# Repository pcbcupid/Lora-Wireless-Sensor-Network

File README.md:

# Lora-Wireless-Sensor-Network

This repo will teach you, how to build a hardware product based on WSN completely from scratch!

We'll walk you through all the stages : 
* [Purpose](https://www.youtube.com/watch?v=e1ifblb0CRQ)
* [Brainstroming -> Feature Selection](https://www.youtube.com/watch?v=0gfi7CeLzbg)
* [Features -> Component Selection](https://youtu.be/0gfi7CeLzbg?t=293)
* [Component -> Schematic Design](https://www.youtube.com/watch?v=nbiwXsXPYxc)
* [Schematic Design -> PCB Design](https://www.youtube.com/watch?v=FiMsBjr6rtk)
* [PCB -> Mechanical Case Design](https://youtu.be/7FC-pByCCXM?si=cBypyLcrKBF-iJE6)
* [Finished Hardware + Code](https://github.com/pcbcupid/Lora-Wireless-Sensor-Network/tree/main/Code)
* [Final Testing](https://www.youtube.com/watch?v=_qDI99OTmmE)

### PCB DESIGN

###### MASTER NODE 

###### SLAVE NODE

### PCB ASSEMBLED 

###### MASTER NODE

###### SLAVE NODE 

### CAD DESIGN 

###### MASTER NODE 

###### SLAVE NODE

### 3D PRINTING 

###### MASTER NODE CASE 

###### SLAVE NODE CASE

### FINAL SETUP 

###### MASTER NODE SETUP 

###### SLAVE NODE SETUP

### DASHBOARD UI

###### MASTER CLOUD DASHBOARD

###### SLAVE CLOUD DASHBOARD

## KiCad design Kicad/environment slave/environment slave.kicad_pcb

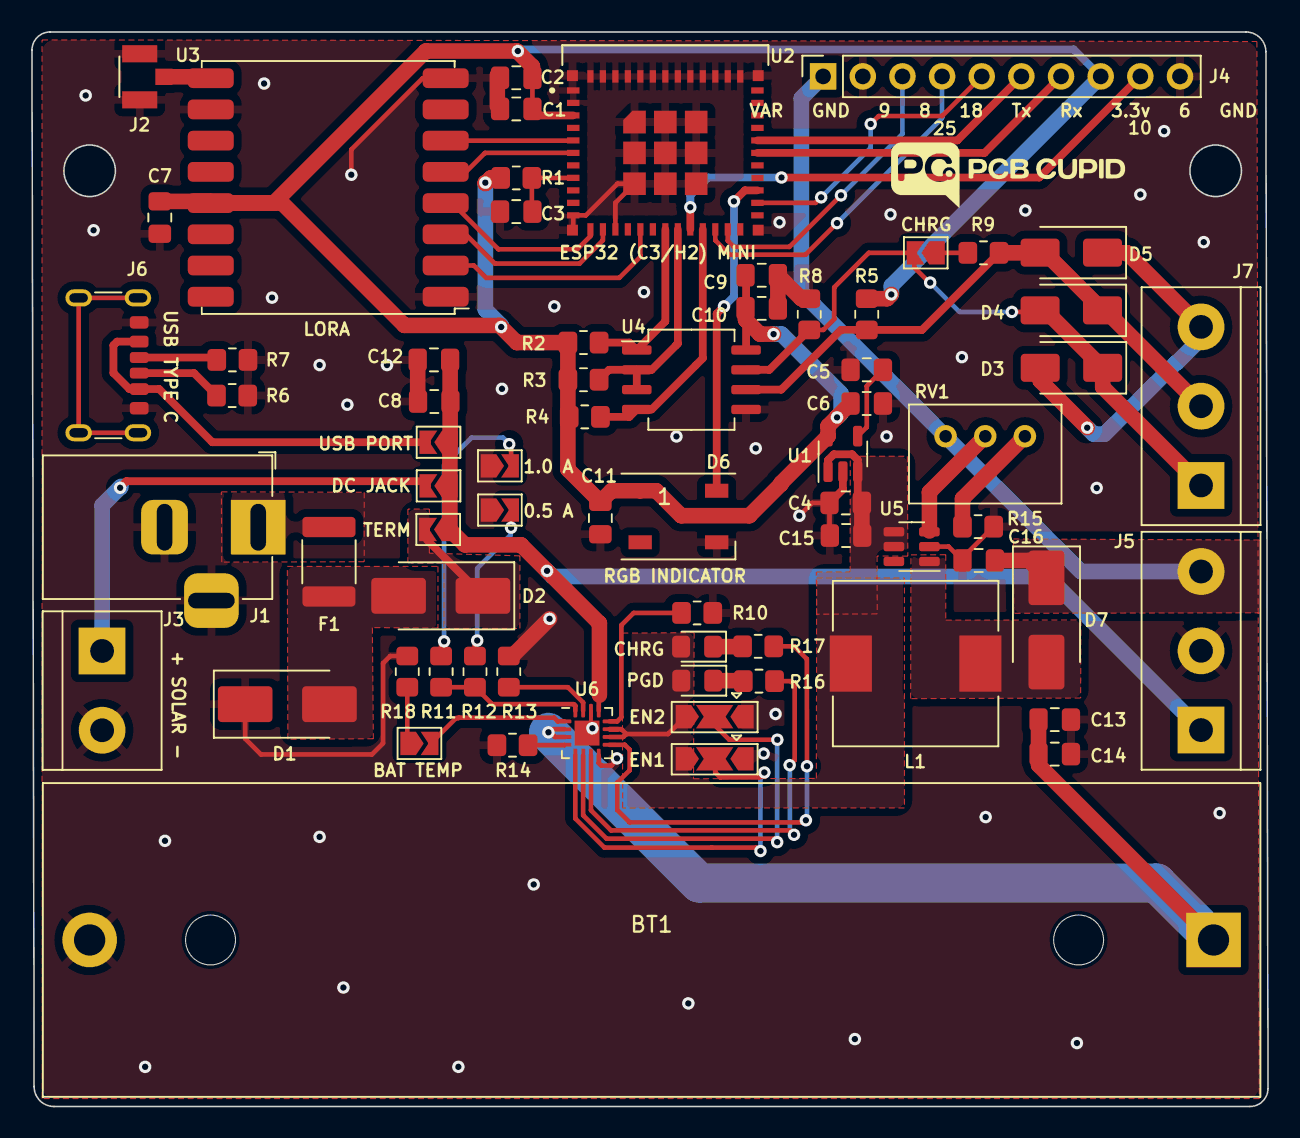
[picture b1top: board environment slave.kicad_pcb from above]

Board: 2 copper layers, 79.2 x 68.8 mm, 69 parts (0 on the bottom side), 52 nets.

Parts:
BT1: Battery_Cell; BatteryHolder_MPD_BH-18650-PC2
C1, C8, C10, C12, C13, C14: 10uf; C_0805_2012Metric_Pad1.18x1.45mm_HandSolder
C2, C4, C7, C11: 0.1uf; C_0805_2012Metric_Pad1.18x1.45mm_HandSolder
C3: 1uf; C_0805_2012Metric_Pad1.18x1.45mm_HandSolder
C5: 470pf; C_0805_2012Metric_Pad1.18x1.45mm_HandSolder
C6: 2.2uf; C_0805_2012Metric_Pad1.18x1.45mm_HandSolder
C9: 0.1uF; C_0805_2012Metric_Pad1.18x1.45mm_HandSolder
C15, C16: 22uf; C_0805_2012Metric_Pad1.18x1.45mm_HandSolder
D1: SMAJ24; D_SMB_Handsoldering
D2: SS34; D_SMB_Handsoldering
D3, D4, D5: SMAJ6.8CA; D_SMA
D6: WS2812B; LED_WS2812B_PLCC4_5.0x5.0mm_P3.2mm
D7: D; D_SMB_Handsoldering
D8: LED - Green; LED_0805_2012Metric_Pad1.15x1.40mm_HandSolder
D9: LED - RED; LED_0805_2012Metric_Pad1.15x1.40mm_HandSolder
F1: Polyfuse; Fuse_1812_4532Metric_Pad1.30x3.40mm_HandSolder
J1: Barrel_Jack; BarrelJack_Horizontal
J2: U.FL-R-SMT_01_; HRS_U.FL-R-SMT_01_
J3: Solar; TerminalBlock_bornier-2_P5.08mm
J4: Conn_01x10; PinSocket_1x10_P2.54mm_Vertical
J5: PWR OUT; TerminalBlock_bornier-3_P5.08mm
J6: USB_C_Receptacle_PowerOnly_6P; USB_C_Receptacle_GCT_USB4125-xx-x_6P_TopMnt_Horizontal
J7: RS485 OUT; TerminalBlock_bornier-3_P5.08mm
JP1, JP2, JP4, JP9: T-JMP; SolderJumper-2_P1.3mm_Open_TrianglePad1.0x1.5mm
JP3: NO; SolderJumper-2_P1.3mm_Open_TrianglePad1.0x1.5mm
JP5: E1; SolderJumper-3_P2.0mm_Open_TrianglePad1.0x1.5mm
JP6: E2; SolderJumper-3_P2.0mm_Open_TrianglePad1.0x1.5mm
JP7: 1A JMP; SolderJumper-2_P1.3mm_Open_TrianglePad1.0x1.5mm
JP8: 0.5A JMP; SolderJumper-2_P1.3mm_Open_TrianglePad1.0x1.5mm
L1: L; L_10.4x10.4_H4.8
R1, R2, R3, R4, R13, R14, R16, R17: 10k; R_0805_2012Metric_Pad1.20x1.40mm_HandSolder
R5, R8: 20k; R_0805_2012Metric_Pad1.20x1.40mm_HandSolder
R6, R7: 5.1k; R_0805_2012Metric_Pad1.20x1.40mm_HandSolder
R9: 120R; R_0805_2012Metric_Pad1.20x1.40mm_HandSolder
R10, R11, R18: 1k; R_0805_2012Metric_Pad1.20x1.40mm_HandSolder
R12: 2k; R_0805_2012Metric_Pad1.20x1.40mm_HandSolder
R15: 2.2k; R_0805_2012Metric_Pad1.20x1.40mm_HandSolder
RV1: 100k; Potentiometer_Bourns_3299W_Vertical
U1: MIC5219-3.3v; SOT-23-5
U2: ESP32-C3-MINI-1U-N4; XCVR_ESP32-C3-MINI-1U-N4
U3: RFM95W-868S2; HOPERF_RFM9XW_SMD
U4: THVD1406; SO-8_5.3x6.2mm_P1.27mm
U5: MT3608; SOT-23-6
U6: BQ24074RGT; VQFN-16-1EP_3x3mm_P0.5mm_EP1.6x1.6mm

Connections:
+3.3V: C1.1, C2.1, C6.1, C7.1, C9.1, C10.1, C11.1, D6.1 (VDD), J4.8, R1.1, R2.1, R3.1, R4.1, R5.1, U1.5 (OUT), U2.3 (3V3), U3.13 (3.3V), U4.8 (VCC)
/Battery Managment Circuit/Bat+: BT1.1 (+), C13.1, C14.1, U6.2 (BAT), U6.3 (BAT)
/COM: D3.2 (A2), D5.1 (A1), J7.3
/DI: R4.2, U2.21 (IO7), U4.4 (DI)
/DTR: R3.2, U2.19 (IO5), U4.2 (~RE), U4.3 (DE)
/GPIO6: J4.9, U2.20 (IO6)
/GPIO8: J4.4, U2.22 (IO8)
/GPIO9: J4.3, U2.23 (IO9)
/GPIO18: J4.5, U2.26 (IO18)
/MISO: U2.16 (IO10), U3.2 (MISO)
/MOSI: U2.13 (IO1), U3.3 (MOSI)
/NSS: U2.6 (IO3), U3.5 (NSS)
/OUT: C4.1, C15.1, D8.2 (A), D9.2 (A), JP5.3 (B), JP6.3 (B), L1.1, U1.1 (IN), U1.3 (EN), U5.4 (EN), U5.5 (IN), U6.10 (OUT), U6.11 (OUT)
/OUT_VAR: C16.1, D7.1 (K), J4.1, J5.3, RV1.3
/R0: R2.2, U2.18 (IO4), U4.1 (RO)
/RESET: U2.5 (IO2), U3.6 (RESET)
/RGB: D6.4 (DIN), U2.27 (IO19)
/SCK: U2.12 (IO0), U3.4 (SCK)
/U0Rxd: J4.7, U2.30 (RXD0)
/U0Txd: J4.6, U2.31 (TXD0)
GND: BT1.2 (-), C1.2, C2.2, C3.2, C4.2, C5.2, C6.2, C7.2, C8.2, C9.2, C10.2, C11.2, C12.2, C13.2, C14.2, C15.2, C16.2, D1.1 (A1), D6.3 (VSS), J1.2, J1.3, J2.1 (GND), J2.2 (GND), J3.2, J4.2, J4.10, J5.2, J6.A12 (GND), J6.B12 (GND), JP5.1 (A), JP6.1 (A), JP7.1 (A), JP8.1 (A), R6.1, R7.1, R8.2, R10.1, R13.1, R14.1, R15.2, R18.2, U1.2 (GND), U2.1 (GND), U2.2 (GND__1), U2.11 (GND__2), U2.14 (GND__3), U2.36 (GND__4), U2.37 (GND__5), U2.38 (GND__6), U2.39 (GND__7), U2.40 (GND__8), U2.41 (GND__9), U2.42 (GND__10), U2.43 (GND__11), U2.44 (GND__12), U2.45 (GND__13), U2.46 (GND__14), U2.47 (GND__15), U2.48 (GND__16), U2.49_1 (GND__17), U2.49_2 (GND__18), U2.49_3 (GND__19), U2.49_4 (GND__20), U2.49_5 (GND__21), U2.49_6 (GND__22), U2.49_7 (GND__23), U2.49_8 (GND__24), U2.49_9 (GND__25), U2.50 (GND__26), U2.51 (GND__27), U2.52 (GND__28), U2.53 (GND__29), U3.1 (GND), U3.8 (GND), U3.10 (GND), U4.5 (GND), U5.2 (GND), U6.8 (VSS), U6.14 (TMR), U6.17 (VSS)
unnamed: D1.2 (A2), D2.2 (A), F1.2
unnamed: D2.1 (K), JP1.2 (B)
unnamed: D3.1 (A1), D4.2 (A2), J7.1, JP3.2 (B), R8.1, U4.7 (B)
unnamed: D4.1 (A1), D5.2 (A2), J7.2, R5.2, R9.2, U4.6 (A)
unnamed: D7.2 (A), L1.2, U5.1 (SW)
unnamed: D8.1 (K), R16.2
unnamed: D9.1 (K), R17.2
unnamed: F1.1, J1.1
unnamed: J2.3 (SIG), U3.9 (ANT)
unnamed: J3.1, JP2.2 (B)
unnamed: J6.A5 (CC1), R7.2
unnamed: J6.B5 (CC2), R6.2
unnamed: JP3.1 (A), R9.1
unnamed: J6.A9 (VBUS), J6.B9 (VBUS), JP4.2 (B)
unnamed: JP5.2 (C), U6.5 (EN2)
unnamed: JP6.2 (C), U6.6 (EN1)
unnamed: JP7.2 (B), R11.1
unnamed: JP8.2 (B), R12.1
unnamed: JP9.1 (A), R18.1
unnamed: JP9.2 (B), U6.1 (TS)
unnamed: R15.1, RV1.1
unnamed: C5.1, U1.4 (BP)
unnamed: C3.1, R1.2, U2.8 (EN)
unnamed: RV1.2, U5.3 (FB)
unnamed: R10.2, U6.12 (ILIM)
unnamed: R11.2, R12.2, U6.16 (ISET)
unnamed: R13.2, U6.15 (ITERM)
unnamed: R14.2, U6.4 (~CE)
unnamed: R17.1, U6.9 (~CHG)
unnamed: R16.1, U6.7 (~PGOOD)
VCC: C8.1, C12.1, J5.1, JP1.1 (A), JP2.1 (A), JP4.1 (A), U6.13 (IN)

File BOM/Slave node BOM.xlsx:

References | Value | Footprint | Quantity
C1, C8, C10, C12, C13, C14 | 10uf | C_0805_2012Metric_Pad1.18x1.45mm_HandSolder | 6
C2, C4, C7, C9, C11 | 0.1uf | C_0805_2012Metric_Pad1.18x1.45mm_HandSolder | 5
C15, C16 | 22uf | C_0805_2012Metric_Pad1.18x1.45mm_HandSolder | 2
C3 | 1uf | C_0805_2012Metric_Pad1.18x1.45mm_HandSolder | 1
C5 | 470pf | C_0805_2012Metric_Pad1.18x1.45mm_HandSolder | 1
C6 | 2.2uf | C_0805_2012Metric_Pad1.18x1.45mm_HandSolder | 1
R1, R2, R3, R4, R13, R14, R16, R17 | 10k | R_0805_2012Metric_Pad1.20x1.40mm_HandSolder | 8
R10, R11, R18 | 1k | R_0805_2012Metric_Pad1.20x1.40mm_HandSolder | 3
R5, R8 | 20k | R_0805_2012Metric_Pad1.20x1.40mm_HandSolder | 2
R6, R7 | 5.1k | R_0805_2012Metric_Pad1.20x1.40mm_HandSolder | 2
R9 | 120R | R_0805_2012Metric_Pad1.20x1.40mm_HandSolder | 1
R12 | 2k | R_0805_2012Metric_Pad1.20x1.40mm_HandSolder | 1
R15 | 2.2k | R_0805_2012Metric_Pad1.20x1.40mm_HandSolder | 1
L1 | L | L_10.4x10.4_H4.8 | 1
D3, D4, D5 | SMAJ6.8CA | D_SMA | 3
D1 | SMAJ24 | D_SMB_Handsoldering | 1
D2 | SS34 | D_SMB_Handsoldering | 1
D6 | WS2812B | LED_WS2812B_PLCC4_5.0x5.0mm_P3.2mm | 1
D7 | D | D_SMB_Handsoldering | 1
D8 | LED - Green | LED_0805_2012Metric_Pad1.15x1.40mm_HandSolder | 1
D9 | LED - RED | LED_0805_2012Metric_Pad1.15x1.40mm_HandSolder | 1
U1 | MIC5219-3.3v | SOT-23-5 | 1
U2 | ESP32-C3-MINI-1U-N4 | XCVR_ESP32-C3-MINI-1U-N4 | 1
U3 | RFM95W-868S2 | HOPERF_RFM9XW_SMD | 1
U4 | MAX485E | SO-8_5.3x6.2mm_P1.27mm | 1
U5 | MT3608 | SOT-23-6 | 1
U6 | BQ24074RGT | VQFN-16-1EP_3x3mm_P0.5mm_EP1.6x1.6mm | 1
F1 | Polyfuse | Fuse_1812_4532Metric_Pad1.30x3.40mm_HandSolder | 1
JP1, JP2, JP4, JP9 | T-JMP | SolderJumper-2_P1.3mm_Open_TrianglePad1.0x1.5mm | 4
BT1 | Battery_Cell | BatteryHolder_MPD_BH-18650-PC2 | 1
JP3 | NO | SolderJumper-2_P1.3mm_Open_TrianglePad1.0x1.5mm | 1
JP5 | E1 | SolderJumper-3_P2.0mm_Open_TrianglePad1.0x1.5mm | 1
JP6 | E2 | SolderJumper-3_P2.0mm_Open_TrianglePad1.0x1.5mm | 1
JP7 | 1A JMP | SolderJumper-2_P1.3mm_Open_TrianglePad1.0x1.5mm | 1
JP8 | 0.5A JMP | SolderJumper-2_P1.3mm_Open_TrianglePad1.0x1.5mm | 1
RV1 | 100k | Potentiometer_Bourns_3299W_Vertical | 1
J1 | Barrel_Jack | BarrelJack_Horizontal | 1
J2 | U.FL-R-SMT_01_ | HRS_U.FL-R-SMT_01_ | 1
J3 | Solar | TerminalBlock_bornier-2_P5.08mm | 1
J4 | Conn_01x10 | PinSocket_1x10_P2.54mm_Vertical | 1
J5 | PWR OUT | TerminalBlock_bornier-3_P5.08mm | 1
J6 | USB_C_Receptacle_PowerOnly_6P | USB_C_Receptacle_GCT_USB4125-xx-x_6P_TopMnt_Horizontal | 1
J7 | RS485 OUT | TerminalBlock_bornier-3_P5.08mm | 1

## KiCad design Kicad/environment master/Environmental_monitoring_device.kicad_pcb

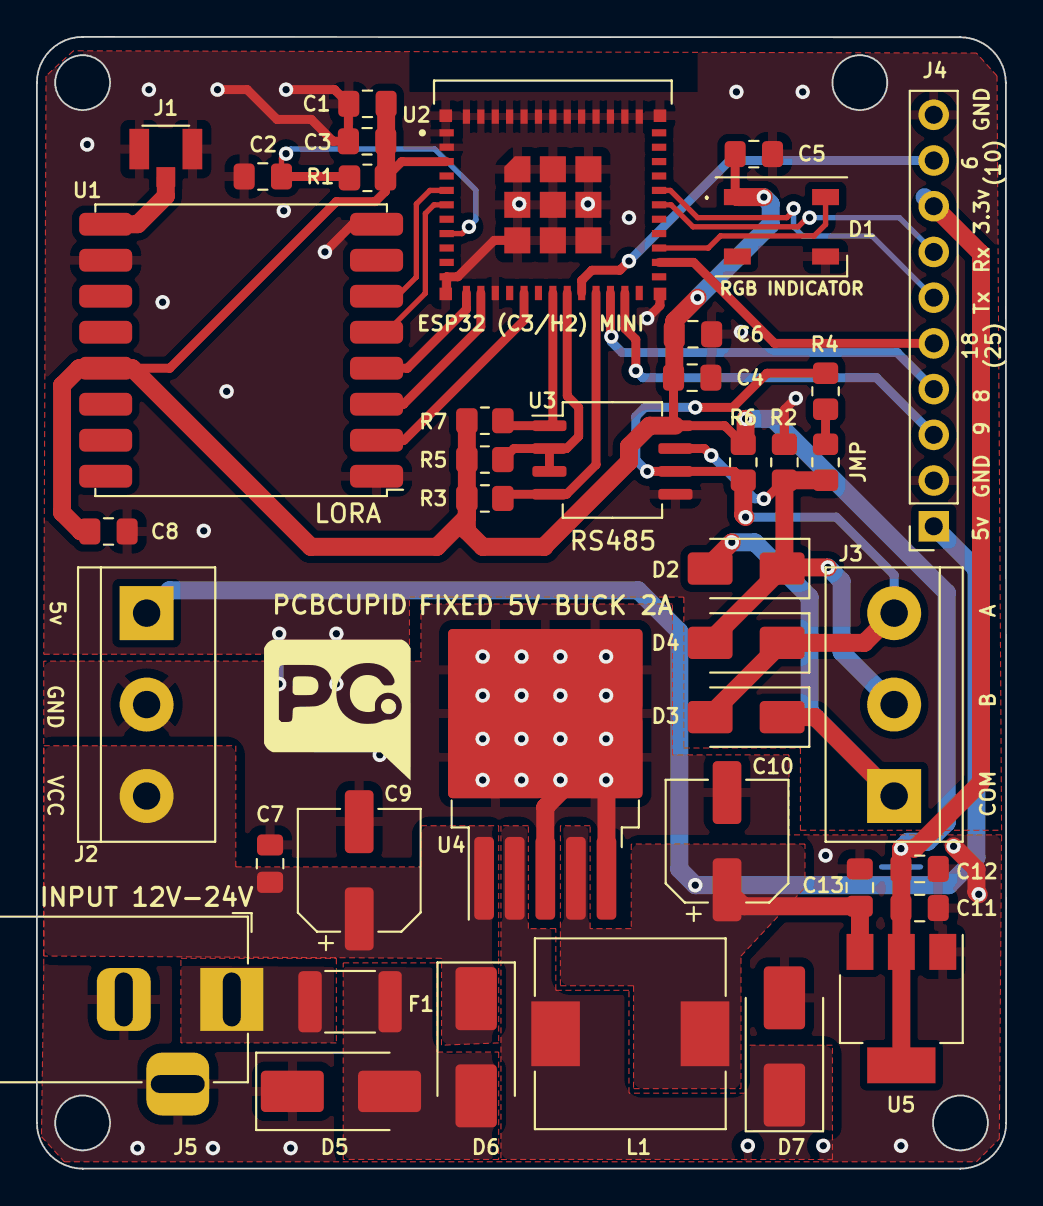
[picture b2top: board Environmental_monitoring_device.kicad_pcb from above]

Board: 2 copper layers, 53.8 x 62.9 mm, 40 parts (0 on the bottom side), 28 nets.

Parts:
C1, C5, C7, C8, C12, C13: 0.1uf; C_0805_2012Metric_Pad1.18x1.45mm_HandSolder
C2, C11: 1uf; C_0805_2012Metric_Pad1.18x1.45mm_HandSolder
C3, C4: 10uf; C_0805_2012Metric_Pad1.18x1.45mm_HandSolder
C6: 0.1uF; C_0805_2012Metric_Pad1.18x1.45mm_HandSolder
C9: 150uf; CP_Elec_6.3x7.7
C10: 220uf; CP_Elec_6.3x7.7
D1: WS2812B; LED_WS2812B_PLCC4_5.0x5.0mm_P3.2mm
D2, D3, D4: SMAJ6.8CA; D_SMA
D5: SMAJ24; D_SMB_Handsoldering
D6, D7: SS34; D_SMB_Handsoldering
F1: Polyfuse; Fuse_1812_4532Metric_Pad1.30x3.40mm_HandSolder
J1: U.FL-R-SMT_01_; HRS_U.FL-R-SMT_01_
J2, J3: RS485 OUT; TerminalBlock_bornier-3_P5.08mm
J4: Conn_01x10; PinSocket_1x10_P2.54mm_Vertical
J5: Barrel_Jack_Switch_Pin3Ring; BarrelJack_Horizontal
JMP: NO; R_0805_2012Metric_Pad1.20x1.40mm_HandSolder
L1: 68uH/35v; L_10.4x10.4_H4.8
R1, R3, R5, R7: 10k; R_0805_2012Metric_Pad1.20x1.40mm_HandSolder
R2, R6: 20k; R_0805_2012Metric_Pad1.20x1.40mm_HandSolder
R4: 120R; R_0805_2012Metric_Pad1.20x1.40mm_HandSolder
U1: RFM95W-868S2; HOPERF_RFM9XW_SMD
U2: ESP32-C3-MINI-1U-N4; XCVR_ESP32-C3-MINI-1U-N4
U3: THVD1406; SO-8_5.3x6.2mm_P1.27mm
U4: LM2596S-5; TO-263-5_TabPin3
U5: AMS1117-3.3; SOT-223-3_TabPin2

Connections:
+3.3V: C1.1, C3.1, C4.1, C5.1, C6.1, C8.1, C11.1, C12.1, D1.1 (VDD), J4.8, R1.1, R3.1, R5.1, R6.1, R7.1, U1.13 (3.3V), U2.3 (3V3), U3.8 (VCC), U5.2 (VO)
+5V: C10.1, C13.1, J2.1, J4.1, L1.2, U4.4 (FB), U5.3 (VI)
/COM: D2.2 (A2), D3.1 (A1), J3.1
/DI: R3.2, U2.21 (IO7), U3.4 (DI)
/DTR: R5.2, U2.19 (IO5), U3.2 (~RE), U3.3 (DE)
/GPIO6: J4.9, U2.20 (IO6)
/GPIO8: J4.4, U2.22 (IO8)
/GPIO9: J4.3, U2.23 (IO9)
/GPIO18: J4.5, U2.26 (IO18)
/MISO: U1.2 (MISO), U2.16 (IO10)
/MOSI: U1.3 (MOSI), U2.13 (IO1)
/NSS: U1.5 (NSS), U2.6 (IO3)
/R0: R7.2, U2.18 (IO4), U3.1 (RO)
/RESET: U1.6 (RESET), U2.5 (IO2)
/RGB: D1.4 (DIN), U2.27 (IO19)
/SCK: U1.4 (SCK), U2.12 (IO0)
/U0Rxd: J4.7, U2.30 (RXD0)
/U0Txd: J4.6, U2.31 (TXD0)
GND: C1.2, C2.2, C3.2, C4.2, C5.2, C6.2, C7.2, C8.2, C9.2, C10.2, C11.2, C12.2, C13.2, D1.3 (VSS), D5.1 (A1), D7.2 (A), J1.1 (GND), J1.2 (GND), J2.2, J4.2, J4.10, J5.2, J5.3, R2.2, U1.1 (GND), U1.8 (GND), U1.10 (GND), U2.1 (GND), U2.2 (GND__1), U2.11 (GND__2), U2.14 (GND__3), U2.36 (GND__4), U2.37 (GND__5), U2.38 (GND__6), U2.39 (GND__7), U2.40 (GND__8), U2.41 (GND__9), U2.42 (GND__10), U2.43 (GND__11), U2.44 (GND__12), U2.45 (GND__13), U2.46 (GND__14), U2.47 (GND__15), U2.48 (GND__16), U2.49_1 (GND__17), U2.49_2 (GND__18), U2.49_3 (GND__19), U2.49_4 (GND__20), U2.49_5 (GND__21), U2.49_6 (GND__22), U2.49_7 (GND__23), U2.49_8 (GND__24), U2.49_9 (GND__25), U2.50 (GND__26), U2.51 (GND__27), U2.52 (GND__28), U2.53 (GND__29), U3.5 (GND), U4.3 (GND), U4.5 (~ON/OFF), U5.1 (GND)
unnamed: D5.2 (A2), D6.2 (A), F1.2
unnamed: D2.1 (A1), D4.2 (A2), J3.2, JMP.2 (B), R2.1, U3.7 (B)
unnamed: D3.2 (A2), D4.1 (A1), J3.3, R4.2, R6.2, U3.6 (A)
unnamed: D7.1 (K), L1.1, U4.2 (OUT)
unnamed: F1.1, J5.1
unnamed: J1.3 (SIG), U1.9 (ANT)
unnamed: JMP.1 (A), R4.1
unnamed: C2.1, R1.2, U2.8 (EN)
VCC: C7.1, C9.1, D6.1 (K), J2.3, U4.1 (VIN)

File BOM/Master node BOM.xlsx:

References | Value | Footprint | Quantity
C1, C5, C6, C7, C8, C12, C13 | 0.1uf | C_0805_2012Metric_Pad1.18x1.45mm_HandSolder | 7
C2, C11 | 1uf | C_0805_2012Metric_Pad1.18x1.45mm_HandSolder | 2
C3, C4 | 10uf | C_0805_2012Metric_Pad1.18x1.45mm_HandSolder | 2
C9 | 150uf | CP_Elec_6.3x7.7 | 1
C10 | 220uf | CP_Elec_6.3x7.7 | 1
R1, R3, R5, R7 | 10k | R_0805_2012Metric_Pad1.20x1.40mm_HandSolder | 4
R2, R6 | 20k | R_0805_2012Metric_Pad1.20x1.40mm_HandSolder | 2
R4 | 120R | R_0805_2012Metric_Pad1.20x1.40mm_HandSolder | 1
L1 | 68uH/35v | L_10.4x10.4_H4.8 | 1
D2, D3, D4 | SMAJ6.8CA | D_SMA | 3
D6, D7 | SS34 | D_SMB_Handsoldering | 2
D1 | WS2812B | LED_WS2812B_PLCC4_5.0x5.0mm_P3.2mm | 1
D5 | SMAJ24 | D_SMB_Handsoldering | 1
U1 | RFM95W-868S2 | HOPERF_RFM9XW_SMD | 1
U2 | ESP32-C3-MINI-1U-N4 | XCVR_ESP32-C3-MINI-1U-N4 | 1
U3 | MAX485E | SO-8_5.3x6.2mm_P1.27mm | 1
U4 | LM2596S-5 | TO-263-5_TabPin3 | 1
U5 | AMS1117-3.3 | SOT-223-3_TabPin2 | 1
F1 | Polyfuse | Fuse_1812_4532Metric_Pad1.30x3.40mm_HandSolder | 1
JMP | NO | R_0805_2012Metric_Pad1.20x1.40mm_HandSolder | 1
J2, J3 | RS485 OUT | TerminalBlock_bornier-3_P5.08mm | 2
J1 | U.FL-R-SMT_01_ | HRS_U.FL-R-SMT_01_ | 1
J4 | Conn_01x10 | PinSocket_1x10_P2.54mm_Vertical | 1
J5 | Barrel_Jack_Switch_Pin3Ring | BarrelJack_Horizontal | 1

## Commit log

2023-12-18 Added dashboar ui images
2023-12-18 updated cad images
2023-12-24 Update README.md
    Updated component -> schematic design video link
2024-01-07 Update README.md
    Updated PCB Layout Video Link
2025-07-02 Completed the repo 1. Added the kicad files for the master & slave node 2. Updated readme with the latest links
2025-07-05 resolves issue #1
